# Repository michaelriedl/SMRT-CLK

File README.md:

# SMRT-CLK
Smart clock / dashboard based on the Raspberry Pi. 

## Building the SMRT CLK
This section will cover the materials and steps needed to build the SMRT CLK.

### Order the PCB
The first step is to order the PCB. You can use the schematics to order the board from your favorite PCB manufacturer or you can use the link below to order it from OSH Park. 

<a href="https://oshpark.com/shared_projects/3NsGFRa8"></img></a>

### Order the Parts
Next you'll need to order the parts using the bill of materials spreadsheet in the */bom/* folder. You can upload the BOM straight to DigiKey and order the parts all at once. You will also need to order some parts from McMaster Carr. The links to the parts are as follows:
+ <https://www.mcmaster.com/94180A331>
+ <https://www.mcmaster.com/94180A307>
+ <https://www.mcmaster.com/93070A064>
+ <https://www.mcmaster.com/93070a275>

### Assembling the PCB
Assembing the PCB is easiest using solder paste and a hot air reflow station. You can refer to the board schematic for component placement. The most difficult component is the 40 pin connector for the screen due to the fine pitch of the pins. Once the PCB is assembled you will need to solder the PCB to the Raspberry Pi Zero. I found that this was easiest to do by first using the screws and brass inserts to hold the PCB to the Pi once the pads are aligned and then using the solder paste syringe to put the paste into the through-hole pins on the Pi. The two can then be reflowed with a hot air reflow station.

### Building the Case
To build the case you will need to 3D print two parts and cut another two parts out of 3mm acrylic. I have included STL files for the parts that need to be printed and an EPS file for the parts that need to be cut. If you do not have access to a laser cutter, I have used <https://ponoko.com> in the past and was really happy with the results.

Once the parts are 3D printed, you will need to sink the brass heated inserts into the parts with a soldering iron. This should be pretty straight forward. There are plenty of videos and guides on the interenet if you need an example of how to set the inserts.

Final assembly of the SMRT CLK should be easy. I would suggest assembling the SMRT CLK in this order:
1. Attach the screen's ribbon cables to the PCB.
2. Secure the Pi into the 3D printed base using the screws.
3. Attach the acrylic lid to the 3D printed base using the screws.
4. Attach the acrylic screen mount to the base using the screws.
5. Place the screen in the 3D printed screen mount and attach it to the acrylic screen mount with the screws.

## Setting Up the SMRT CLK
There are just a few files that need to be copied to the Pi itself and then some of them need to be compiled. These files are located in the */distro/* folder. We will start first with the device tree overlays which need to be transfered to the Pi and compiled.

### Device Tree Overlays
I have written some device tree settings that need to be compiled into device tree overlays and placed in the proper folder. The overlays do the following:
1. *dpi565.dts* - This sets the GPIO that we use for the screen to their alternate function which is DPI output.
2. *pullup.dts* - This sets the pullup resistors for the GPIO pins that we are using for I2C. We are using I2C to communicate with the touch screen controller.
3. *touchscreen.dts* - This sets the driver to use with the I2C touch controller. It also registers a GPIO pin to use as a hardware interrupt for the touch controller.
The device tree overlays should be compiled with the following commands:
```
sudo dtc -I dts -O dtb -o /boot/overlays/dpi565.dtbo dpi565.dts
sudo dtc -I dts -O dtb -o /boot/overlays/pullup.dtbo pullup.dts
sudo dtc -I dts -O dtb -o /boot/overlays/touchscreen.dtbo touchscreen.dts
```

### Boot Configuration
I also have included a *config.txt* that should replace the existing one in the Raspbian */boot/* folder. The purpose of the file configuration file is to tell Raspbian to load the device tree overlays we compiled. Additionally, the configuration file has the settings (resolution, timings, etc...) for the LCD display.

### Touch Screen Calibration
Once the device tree overlays and boot configuration are properly setup, the display and touch screen should work after rebooting the Pi. The final step is to calibrate the touch screen. I found these calibration values through trial and error. Eventually I would like to write a script that does the calibration by having the user touch calibration points on the screen. The screen can be calibrated with the following commands:
```
DISPLAY=:0 xinput set-prop 'EP0790M09' 'Coordinate Transformation Matrix' 1 0 -1 0 1 0 0 0 1
DISPLAY=:0 xinput set-prop 'EP0790M09' 'libinput Calibration Matrix' 6.5 0 1 0 10 0 0 0 1
```
This calibration only lasts as long as the Pi is on. To make the calibration permanent, the commands need to be placed in a script and executed once the Pi is on and the device tree overlays have been loaded. There are various ways to do this depending on your application and version of Raspbian.

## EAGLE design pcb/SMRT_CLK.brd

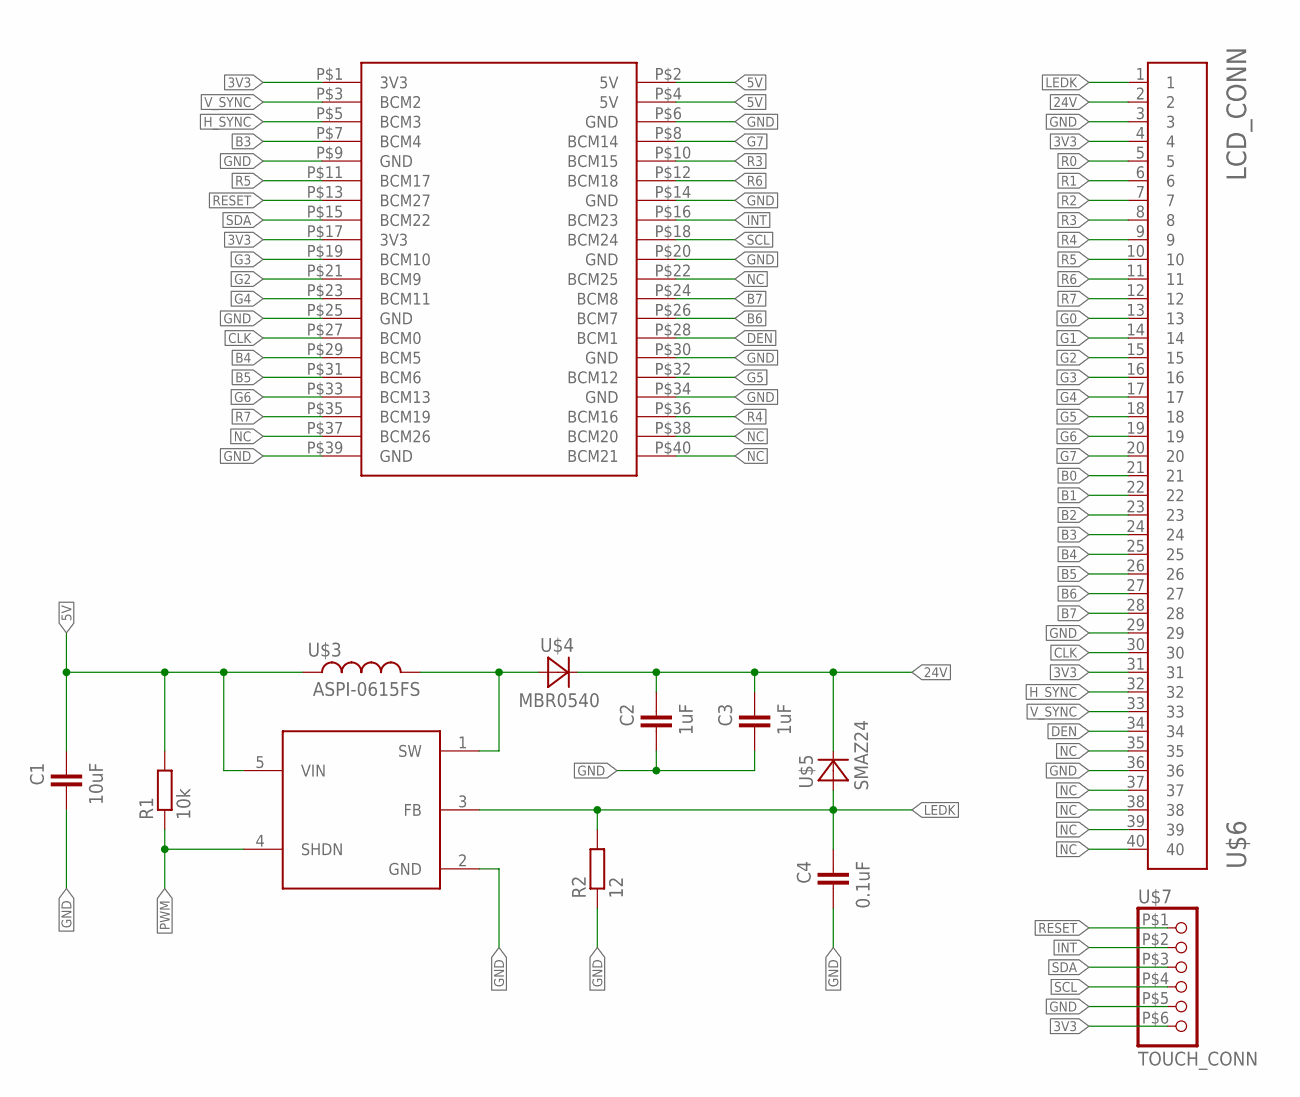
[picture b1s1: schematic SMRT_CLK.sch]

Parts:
C1: 10uF; C0805
C2, C3: 1uF; C0805
C4: 0.1uF; C0805
R1: 10k; R0805
R2: 12; R0805
U$1: SMRT_CLK; FULL_BOARD
U$2: FAN5333BSX; SOT23-5
U$3: ASPI-0615FS; CUST_IND
U$4: MBR0540; SOD-123_MINI-SMA
U$5: SMAZ24; DO-214AC
U$6: LCD_CONN; 4-1734839-0
U$7: TOUCH_CONN; 052207

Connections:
3V3: U$1.P$1 (3V3), U$1.P$17 (3V3), U$6.4, U$6.31, U$7.P$6 (6)
5V: C1.2, R1.2, U$1.P$2 (5V), U$1.P$4 (5V), U$2.5 (VIN), U$3.P$1 (1)
24V: C2.2, C3.2, U$4.C, U$5.C, U$6.2
B0: U$6.21
B1: U$6.22
B2: U$6.23
B3: U$1.P$7 (BCM4), U$6.24
B4: U$1.P$29 (BCM5), U$6.25
B5: U$1.P$31 (BCM6), U$6.26
B6: U$1.P$26 (BCM7), U$6.27
B7: U$1.P$24 (BCM8), U$6.28
CLK: U$1.P$27 (BCM0), U$6.30
DEN: U$1.P$28 (BCM1), U$6.34
G0: U$6.13
G1: U$6.14
G2: U$1.P$21 (BCM9), U$6.15
G3: U$1.P$19 (BCM10), U$6.16
G4: U$1.P$23 (BCM11), U$6.17
G5: U$1.P$32 (BCM12), U$6.18
G6: U$1.P$33 (BCM13), U$6.19
G7: U$1.P$8 (BCM14), U$6.20
GND: C1.1, C2.1, C3.1, C4.1, R2.1, U$1.P$6 (GND), U$1.P$9 (GND), U$1.P$14 (GND), U$1.P$20 (GND), U$1.P$25 (GND), U$1.P$30 (GND), U$1.P$34 (GND), U$1.P$39 (GND), U$2.2 (GND), U$6.3, U$6.29, U$6.36, U$7.P$5 (5)
H_SYNC: U$1.P$5 (BCM3), U$6.32
INT: U$1.P$16 (BCM23), U$7.P$2 (2)
LEDK: C4.2, R2.2, U$2.3 (FB), U$5.A, U$6.1
unnamed: U$2.1 (SW), U$3.P$2 (2), U$4.A
NC: U$1.P$22 (BCM25), U$1.P$37 (BCM26), U$1.P$38 (BCM20), U$1.P$40 (BCM21), U$6.35, U$6.37, U$6.38, U$6.39, U$6.40
PWM: R1.1, U$2.4 (SHDN)
R0: U$6.5
R1: U$6.6
R2: U$6.7
R3: U$1.P$10 (BCM15), U$6.8
R4: U$1.P$36 (BCM16), U$6.9
R5: U$1.P$11 (BCM17), U$6.10
R6: U$1.P$12 (BCM18), U$6.11
R7: U$1.P$35 (BCM19), U$6.12
RESET: U$1.P$13 (BCM27), U$7.P$1 (1)
SCL: U$1.P$18 (BCM24), U$7.P$4 (4)
SDA: U$1.P$15 (BCM22), U$7.P$3 (3)
V_SYNC: U$1.P$3 (BCM2), U$6.33

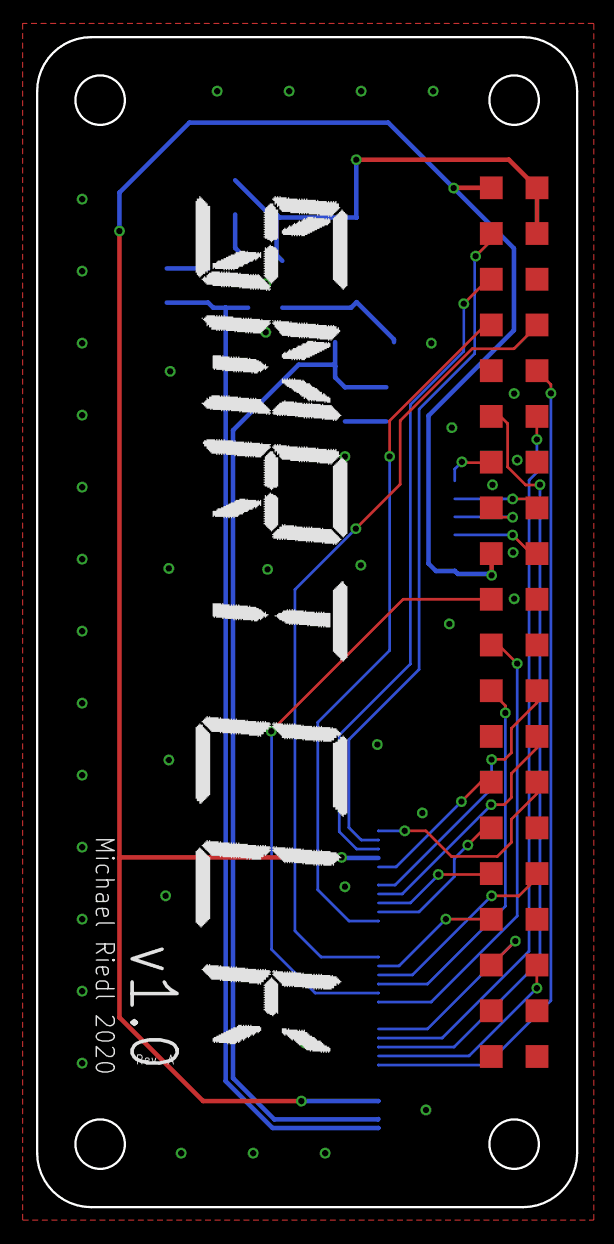
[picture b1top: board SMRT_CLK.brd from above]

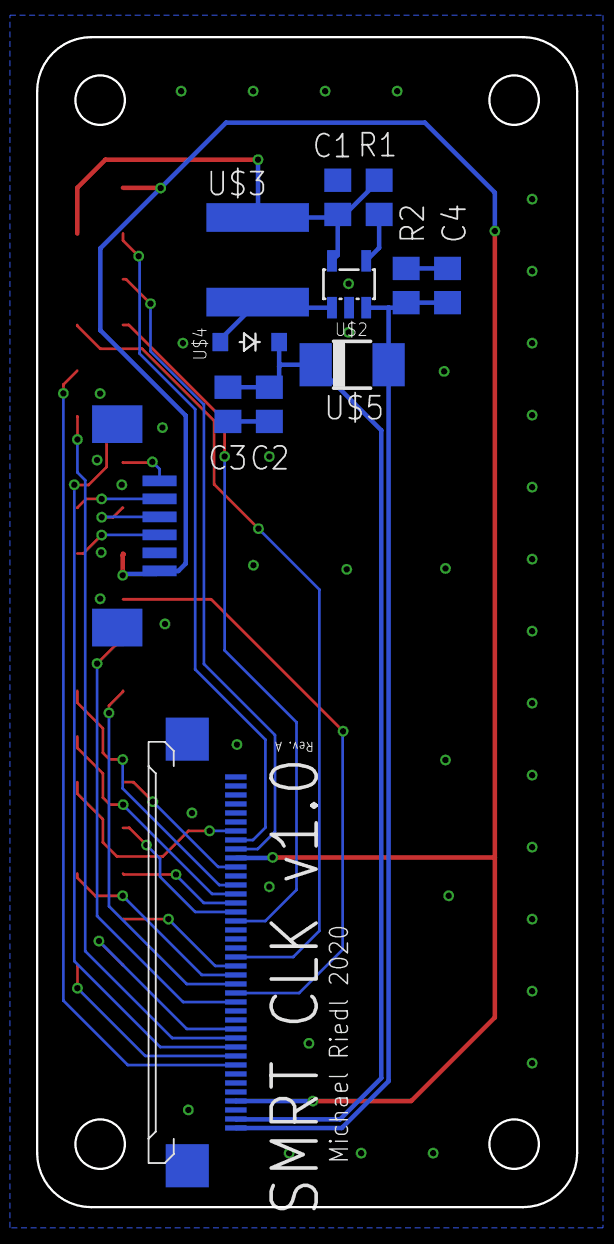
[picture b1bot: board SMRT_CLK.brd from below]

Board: 2 copper layers, 30.0 x 65.0 mm, 13 parts (12 on the bottom side), 32 nets.

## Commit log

2020-02-07 Initial dump
2020-02-07 Added pics
2020-02-08 Added PCB
